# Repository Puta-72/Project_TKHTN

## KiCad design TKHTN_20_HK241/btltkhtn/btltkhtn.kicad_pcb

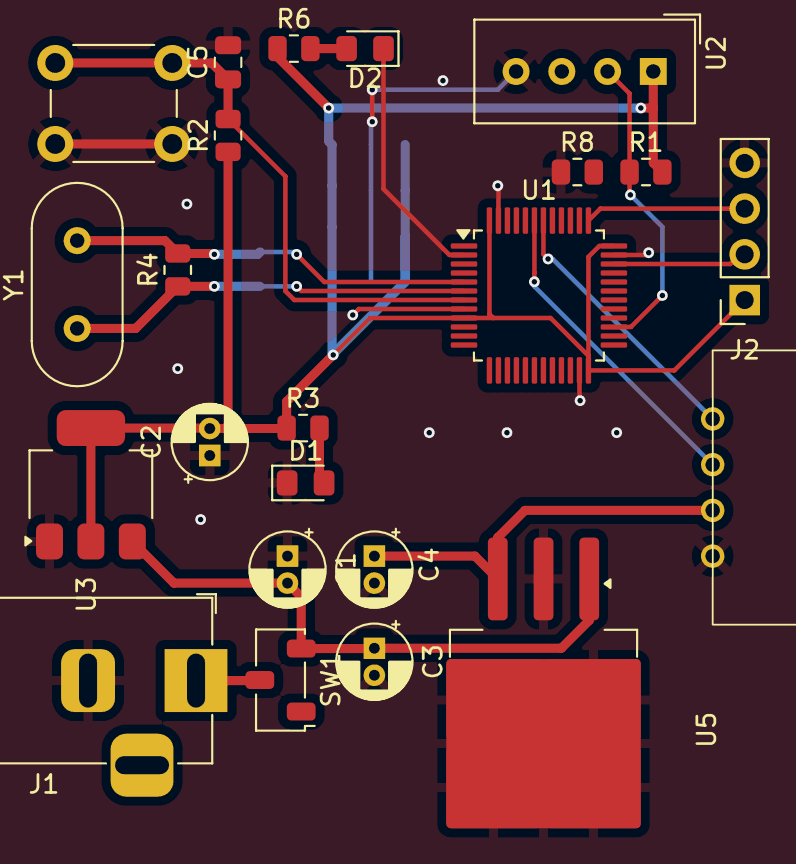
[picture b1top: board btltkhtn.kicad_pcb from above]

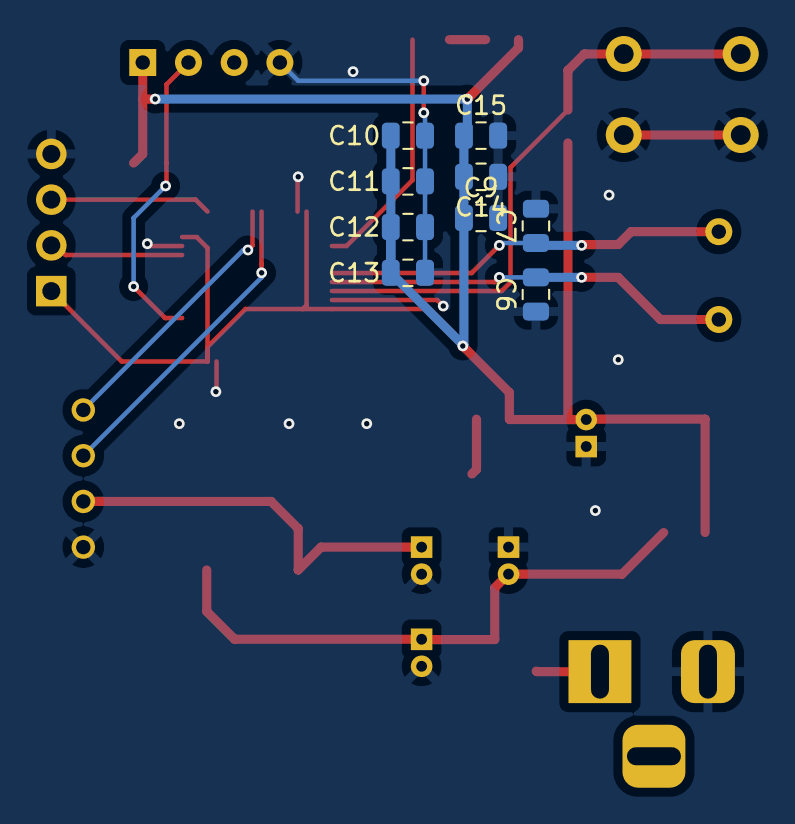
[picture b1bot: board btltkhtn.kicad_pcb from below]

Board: 2 copper layers, 36 parts (9 on the bottom side), 17 nets.

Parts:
C1, C2, C3, C4: 10uF; CP_Radial_D4.0mm_P1.50mm
C5: 1uF; C_0805_2012Metric
C6, C7: 20pF; C_0805_2012Metric
C9: 0,1uF; C_0805_2012Metric
C10, C11, C12, C13, C15: 0.1uF; C_0805_2012Metric
C14: 10uF; C_0805_2012Metric
D1, D2: LED; LED_0805_2012Metric_Pad1.15x1.40mm_HandSolder
H1, H2, H3, H4: MountingHole; MountingHole_2.1mm
J1: Jack-DC; BarrelJack_Horizontal
J2: Conn_01x04_Pin; PinSocket_1x04_P2.54mm_Vertical
MODULE_I2C1: MODULE_I2C
R1, R8: 10k; R_0805_2012Metric
R2: 10K; R_0805_2012Metric
R3, R6: 510; R_0805_2012Metric
R4: 1M; R_0805_2012Metric
SW1: SW_Nidec_CAS-120A1; Nidec_Copal_CAS-120A
SW3: SW_Push; SW_PUSH_6mm
U1: STM32F103C8Tx; LQFP-48_7x7mm_P0.5mm
U2: DHT11; Aosong_DHT11_5.5x12.0_P2.54mm
U3: AMS1117; SOT-223-3_TabPin2
U5: LM7805_TO220; TO-263-3_TabPin2
Y1: 8Mhz; Crystal_HC49-U_Vertical

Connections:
/3v3: C2.2, C9.1, C10.1, C11.1, C12.1, C13.1, C14.2, C15.1, J2.1, R1.2, R2.1, R3.1, R6.1, U1.9 (VDDA), U1.24 (VDD), U1.36 (VDD), U1.48 (VDD), U2.1 (VDD), U3.2 (VO)
/5v: C4.1, MODULE_I2C1.18 (VCC), U5.3 (VO)
/GND: C1.1, C2.1, C3.2, C4.2, C5.2, C6.1, C7.2, C9.2, C10.2, C11.2, C12.2, C13.2, C14.1, C15.2, D1.1 (K), J1.2, J2.4, MODULE_I2C1.17 (GND), R8.1, SW3.1, U1.8 (VSSA), U1.23 (VSS), U1.35 (VSS), U1.47 (VSS), U2.4 (GND), U3.1 (ADJ), U5.2 (GND)
/OSCIN: C7.1, R4.2, U1.5 (PD0), Y1.2
/OSCOUT: C6.2, R4.1, U1.6 (PD1), Y1.1
/PB14: R1.1, U1.27 (PB14), U2.2 (DATA)
/PC13: D2.1 (K), U1.2 (PC13)
/RESET: C5.1, R2.2, SW3.2, U1.7 (NRST)
/SCL: MODULE_I2C1.20 (SCL), U1.42 (PB6)
/SDA: MODULE_I2C1.19 (SDA), U1.43 (PB7)
/SWCLK: J2.3, U1.37 (PA14)
/SWDIO: J2.2, U1.34 (PA13)
unnamed: D1.2 (A), R3.2
unnamed: D2.2 (A), R6.2
unnamed: C1.2, C3.1, SW1.3 (A), U3.3 (VI), U5.1 (VI)
unnamed: J1.1, SW1.2 (B)
unnamed: R8.2, U1.44 (BOOT0)

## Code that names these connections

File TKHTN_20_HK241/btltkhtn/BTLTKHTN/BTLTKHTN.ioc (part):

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Mcu.Name=STM32F103C(8-B)Tx
Mcu.Package=LQFP48
Mcu.UserName=STM32F103C8Tx
PA13.Mode=Serial_Wire
PA13.Signal=SYS_JTMS-SWDIO
PA14.Mode=Serial_Wire
PA14.Signal=SYS_JTCK-SWCLK
PB14.Signal=GPIO_Output
PB6.Mode=I2C
PB6.Signal=I2C1_SCL
PB7.Mode=I2C
PB7.Signal=I2C1_SDA
PD0-OSC_IN.Mode=HSE-External-Oscillator
PD0-OSC_IN.Signal=RCC_OSC_IN
PD1-OSC_OUT.Mode=HSE-External-Oscillator
PD1-OSC_OUT.Signal=RCC_OSC_OUT
RCC.SYSCLKFreq_VALUE=72000000
RCC.SYSCLKSource=RCC_SYSCLKSOURCE_PLLCLK
board=custom

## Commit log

2024-10-23 thêm 20_L01_BTVN.docx
2024-12-11 Add all files
